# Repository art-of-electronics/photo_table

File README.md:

# Photo table

<div align="center">
  
</div>

Folders contain following files:
1) CAD: table step and stl files for NEMA17 and NEMA23 type stepper motors, 
2) GERB: gerber files for production (upload to JLCPCB and have fun), 
3) Kicad: Kicad 6 project files, so you can fiddle to your hert's content.

I have also uploaded a schematic in pdf file and sample code in micropython for Wemos D1 mini (ESP8266) and Wemos S2 (ESP32) boards in main folder. 

**Tripple check GPIOs on your version of ESP before uploading the code!**

---

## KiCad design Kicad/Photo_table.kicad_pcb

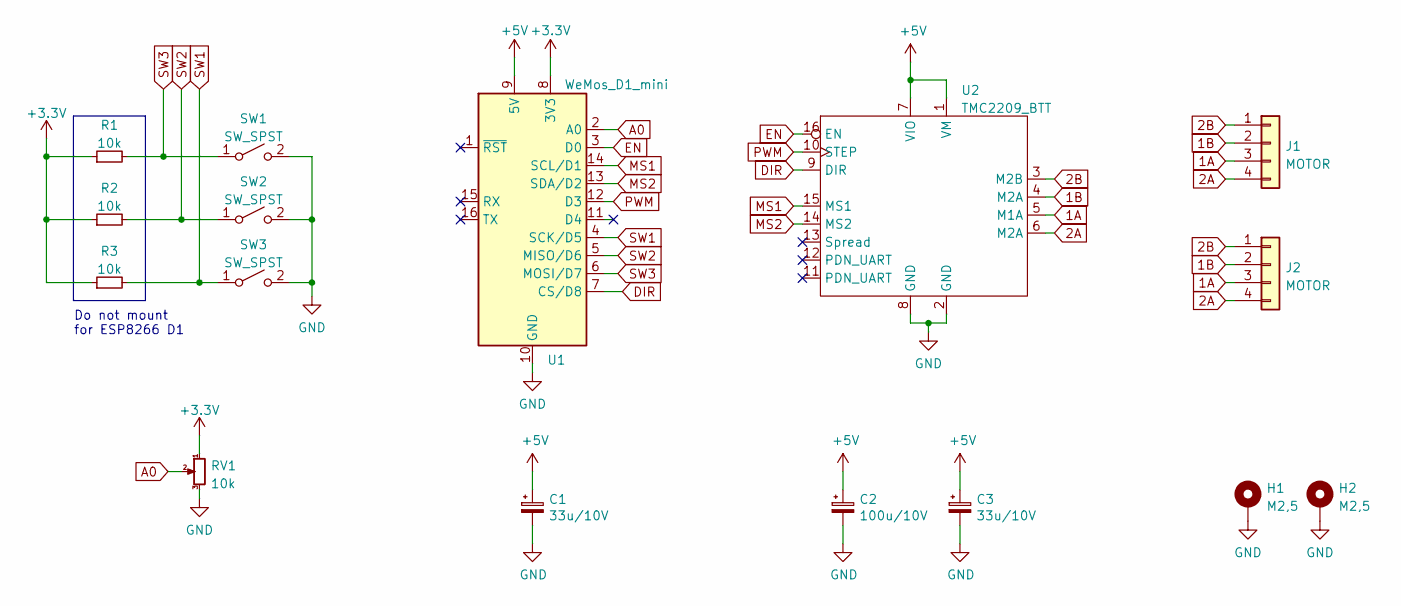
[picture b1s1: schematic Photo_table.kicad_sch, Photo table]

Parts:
C1, C3: 33u/10V; C_Elec_5x5.4
C2: 100u/10V; C_Elec_8x6.2
H1, H2: M2,5; MountingHole_2.5mm_Pad_Via
J1: MOTOR; PinHeader_1x04_P2.54mm_Vertical
J2: MOTOR; TLZ24V-5.0-4
R1, R2, R3: 10k; R_1206_3216Metric
RV1: 10k; POT9x11
SW1, SW2, SW3: SW_SPST; SW_PUSH_6mm
U1: WeMos_D1_mini; WEMOS_D1_mini_light
U2: TMC2209_BTT; TMC2209_THT

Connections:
1A: J1.3, J2.3, U2.5 (M1A)
1B: J1.2, J2.2, U2.4 (M2A)
2A: J1.4, J2.4, U2.6 (M2A)
2B: J1.1, J2.1, U2.3 (M2B)
+3V3: R1.1, R2.1, R3.1, RV1.1, U1.8 (3V3)
+5V: C1.1, C2.1, C3.1, U1.9 (5V), U2.1 (VM), U2.7 (VIO)
A0: RV1.2, U1.2 (A0)
DIR: U1.7 (CS/D8), U2.9 (DIR)
EN: U1.3 (D0), U2.16 (EN)
GND: C1.2, C2.2, C3.2, H1.1, H2.1, RV1.3, SW1.2 (B), SW2.2 (B), SW3.2 (B), U1.10 (GND), U2.2 (GND), U2.8 (GND)
MS1: U1.14 (SCL/D1), U2.15 (MS1)
MS2: U1.13 (SDA/D2), U2.14 (MS2)
PWM: U1.12 (D3), U2.10 (STEP)
SW1: R3.2, SW3.1 (A), U1.4 (SCK/D5)
SW2: R2.2, SW2.1 (A), U1.5 (MISO/D6)
SW3: R1.2, SW1.1 (A), U1.6 (MOSI/D7)

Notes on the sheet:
Do not mount for ESP8266 D1

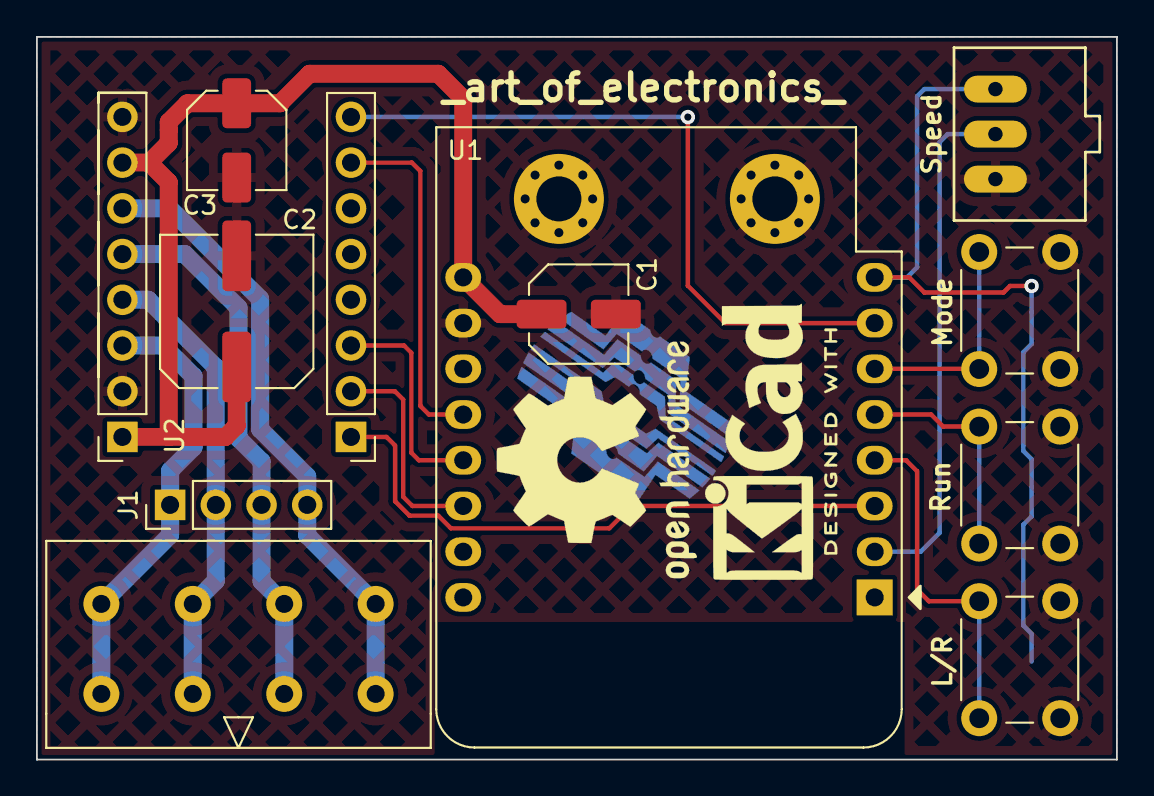
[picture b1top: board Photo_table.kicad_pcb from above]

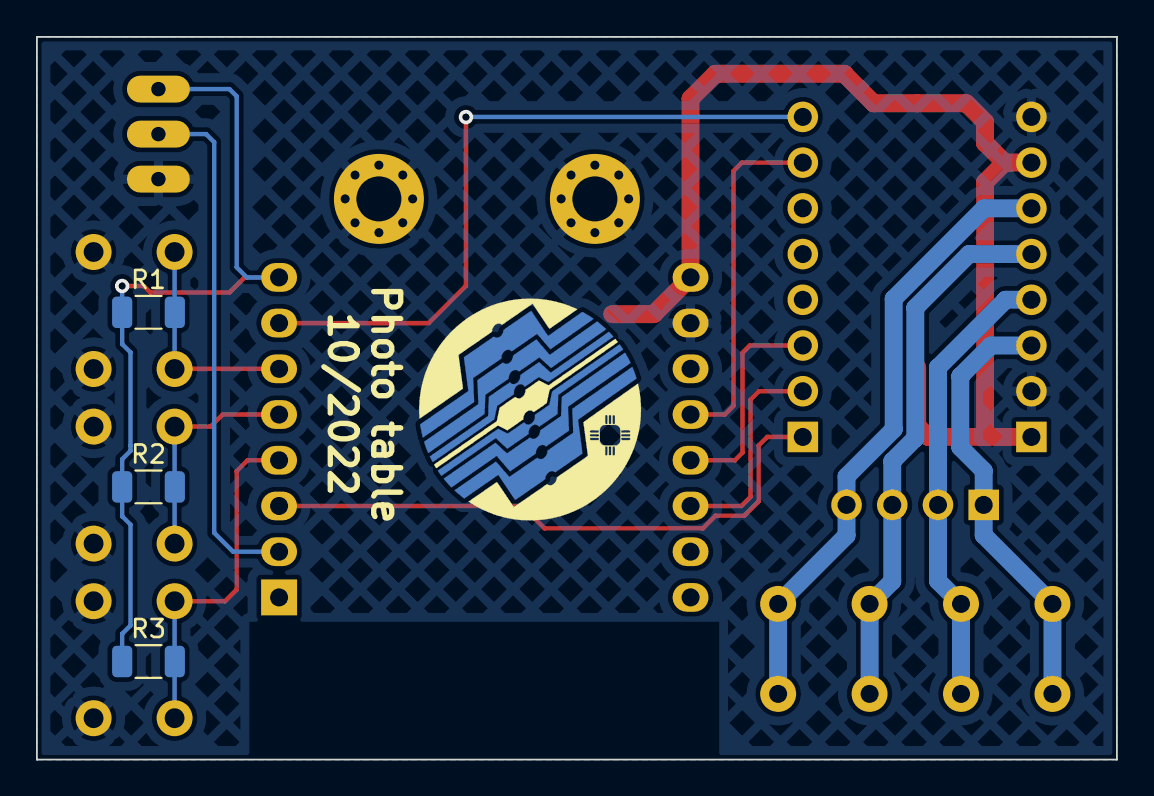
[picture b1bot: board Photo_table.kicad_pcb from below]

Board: 2 copper layers, 60.0 x 40.1 mm, 16 parts (3 on the bottom side), 16 nets.

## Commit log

2025-07-14 Readme update
